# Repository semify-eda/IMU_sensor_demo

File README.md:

# IMU_sensor_demo
Contains the files for PCB and Code for the demo of a ASM330LHHXG1 IMU sensor with Smartwave

> cd python
> pip install -r requirements.txt
> python imu_demo.py

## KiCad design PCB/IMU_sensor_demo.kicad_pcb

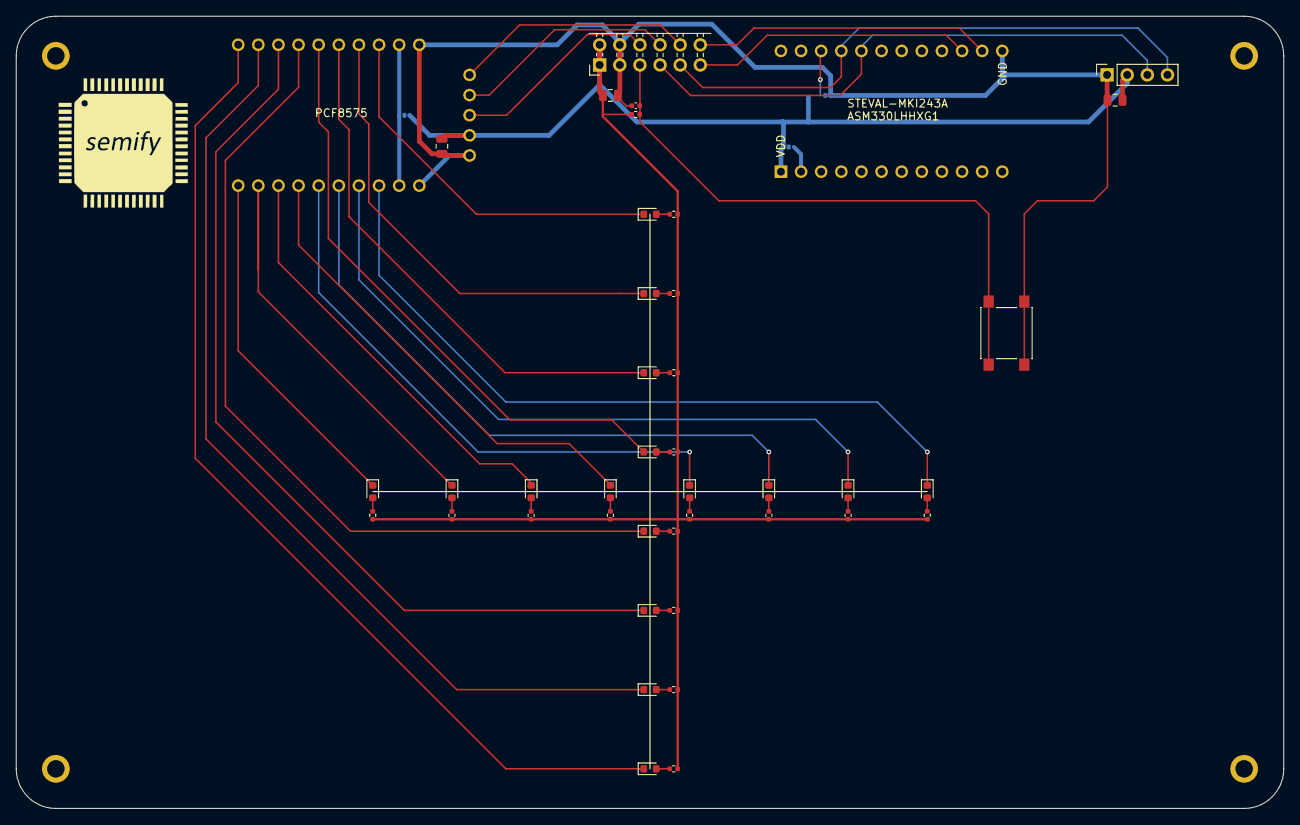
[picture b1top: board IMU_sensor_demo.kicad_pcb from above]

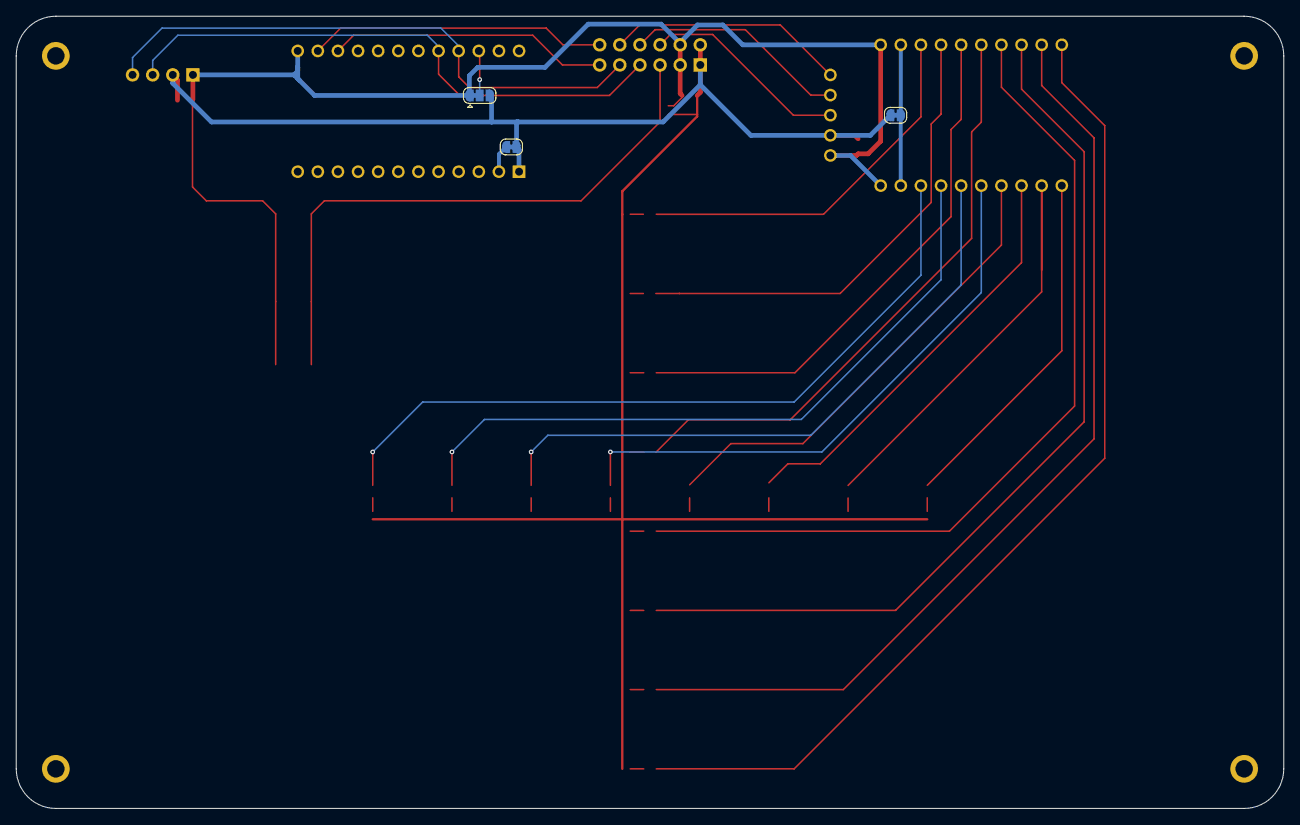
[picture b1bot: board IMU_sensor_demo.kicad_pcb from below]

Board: 2 copper layers, 160.0 x 100.0 mm, 49 parts (3 on the bottom side), 45 nets.

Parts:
C101, C102, C103: 47u; C_0805_2012Metric
C104: 100n; C_1005_(0402)
D101, D102, D103, D104, D105, D106, D107, D108, D109, D110, D111, D112, D113, D114, D115, D116: 0603_LED_Red; LED_0603_1608Metric
H101, H102, H103, H104: MountingHole; MountingHole_2.2mm_M2_ISO7380_Pad
J101: Conn_02x06_Odd_Even; PinHeader_2x06_P2.54mm_Horizontal_less_silk
J102: Conn_01x04_f; PinSocket_1x04_P2.54mm_Vertical
JP101, JP102: Jumper_2; SolderJumper-2_P1.3mm_Bridged
JP103: Jumper_3; SolderJumper-3
R101, R102, R103, R104, R105, R106, R107, R108, R109, R110, R111, R112, R113, R114, R115, R116, R117: 680R; R_1005_(0402)
SW101: Switch; SW_SPST_PTS645
U101: PCF8575_Module
U102: MKI243A_Module; STEVAL-MKI243A_Module

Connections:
+3V3: C101.1, C102.1, C103.1, J101.1, J101.2, J102.2, JP101.1 (A), JP102.1 (A), JP103.3 (B), R101.1, R102.1, R103.1, R104.1, R105.1, R106.1, R107.1, R108.1, R109.1, R110.1, R111.1, R112.1, R113.1, R114.1, R115.1, R116.1, R117.1, U101.4 (VCC), U102.1 (VDD)
/button: C104.1, J101.5, R101.2, SW101.1
/imu_int1: J101.12, U102.14 (INT1)
/imu_int2: J101.11, U102.15 (INT2)
/imu_sdo: JP103.2 (C), U102.22 (SDO)
/p0: D101.1 (K), U101.13 (P0)
/p1: D103.1 (K), U101.12 (P1)
/p2: D105.1 (K), U101.11 (P2)
/p3: D107.1 (K), U101.10 (P3)
/p4: D109.1 (K), U101.9 (P4)
/p5: D111.1 (K), U101.8 (P5)
/p6: D113.1 (K), U101.7 (P6)
/p7: D115.1 (K), U101.6 (P7)
/p10: D102.1 (K), U101.16 (P10)
/p11: D104.1 (K), U101.17 (P11)
/p12: D106.1 (K), U101.18 (P12)
/p13: D108.1 (K), U101.19 (P13)
/p14: D110.1 (K), U101.20 (P14)
/p15: D112.1 (K), U101.21 (P15)
/p16: D114.1 (K), U101.22 (P16)
/p17: D116.1 (K), U101.23 (P17)
/pcf_int_n: J101.10, U101.1 (~INT)
/scl: J101.7, J102.3, U102.20 (SCL)
/scl2: J101.8, U101.2 (SCL)
/sda: J101.9, J102.4, U102.21 (SDA)
/sda2: J101.6, U101.3 (SDA)
/vdd: JP101.2 (B), U101.14 (VDD), U101.24 (VDD)
/vdd_io: JP102.2 (B), U102.2 (VDD_IO)
GND: C101.2, C102.2, C103.2, C104.2, J101.3, J101.4, J102.1, JP103.1 (A), SW101.2, U101.5 (GND), U101.15 (GND), U101.25 (GND), U102.13 (GND)
unnamed: D101.2 (A), R102.2
unnamed: D102.2 (A), R103.2
unnamed: D103.2 (A), R104.2
unnamed: D104.2 (A), R105.2
unnamed: D105.2 (A), R106.2
unnamed: D106.2 (A), R107.2
unnamed: D107.2 (A), R108.2
unnamed: D108.2 (A), R109.2
unnamed: D109.2 (A), R110.2
unnamed: D110.2 (A), R111.2
unnamed: D111.2 (A), R112.2
unnamed: D112.2 (A), R113.2
unnamed: D113.2 (A), R114.2
unnamed: D114.2 (A), R115.2
unnamed: D115.2 (A), R116.2
unnamed: D116.2 (A), R117.2

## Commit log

2024-03-18 empty PCB project
2024-03-19 production run for RevA of demo board
2024-03-19 Added IMU demo script and dependencies
2024-03-25 Updated IMU demo script for new PCB
2024-03-25 Fixed typo
2024-04-03 Updated python script
2024-04-04 Updated requirements for 2.0.0 release
2024-04-08 Added a description for starting the demo
2024-04-17 Added exception handling
2024-05-24 add error handling to imu demo
2024-05-27 update imu scripts
2024-06-03 add fall detection to IMU demo
2024-06-04 add fix for stim mem to imu demo
2024-06-04 finalize IMU demo for webinar
2024-06-04 added soc reset on script startup
2024-06-04 add debug script
2024-06-04 add debug functions
2024-06-05 add button label to smartwave display
2024-06-05 manually configure i2ct
2024-10-04 update imu demo path and io expander address
2024-10-10 rename python directory to scripts
